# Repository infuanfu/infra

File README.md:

infra
=====

INFuanfu Rapid Accelerator

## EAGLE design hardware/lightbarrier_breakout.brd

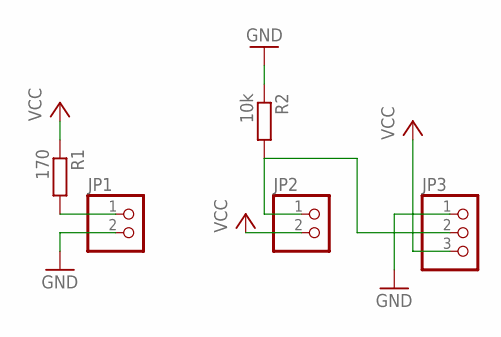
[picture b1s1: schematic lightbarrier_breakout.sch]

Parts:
JP1, JP2: PINHD-1X2; 1X02
JP3: PINHD-1X3/90; 1X03/90
R1: 170; R0805
R2: 10k; R0805

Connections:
GND: JP1.2, JP3.1, R2.1
unnamed: JP1.1, R1.2
unnamed: JP2.1, JP3.2, R2.2
VCC: JP2.2, JP3.3, R1.1

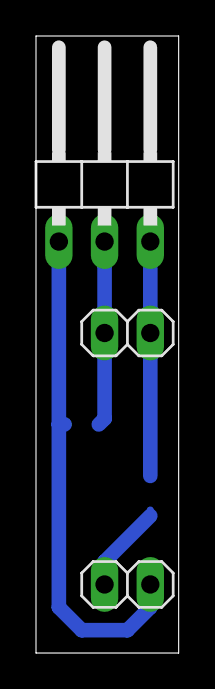
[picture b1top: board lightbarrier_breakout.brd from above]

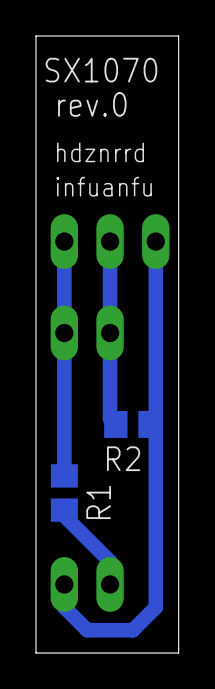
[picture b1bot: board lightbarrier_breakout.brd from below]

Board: 2 copper layers, 7.9 x 34.3 mm, 5 parts (2 on the bottom side), 4 nets.

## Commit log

2014-06-22 test code
2014-06-22 science!
2014-07-14 rev 0 of SX1070 breakout board
2014-07-14 added .gitignore
2014-07-14 experiments with newly wound single coil
2014-07-14 fixed tiny airwire
2014-07-16 removed uneccesary item names. text now on silkscreen layer
